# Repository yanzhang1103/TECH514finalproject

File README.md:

# TECH514finalproject
CatGuard
Proximity-Based Alert & Visualization System

A two-device proximity sensing system that detects how close an object or person is and provides intuitive physical feedback through a gauge needle and LED indicators. The system focuses on translating continuous proximity data into stable, non-screen-based feedback that can support spatial awareness and proximity alerts.

1. Sensor Device: Handheld Proximity Sensor

The sensor device is a compact, handheld proximity-sensing unit designed to detect nearby objects and transmit processed proximity data wirelessly to a separate display device. It emphasizes directional sensing and portable, USBC-powered operation.

Hardware Components

Microcontroller: ESP32-C3 

Distance Sensor: Sharp GP2Y0A21YK0F infrared distance sensor

Status Indicator: LED

Battery: 3.7V LiPo battery

How It Works

The infrared distance sensor continuously measures the distance between the device and nearby objects. The ESP32-C3 samples the analog sensor output and applies basic digital signal processing, including smoothing and thresholding, to reduce noise and generate a stable proximity level. This processed proximity data is transmitted to the display device using ESP-NOW.

2. Display Device: Proximity Gauge Display

The display device is a standalone physical interface that visualizes proximity information received from the sensor device. It provides continuous, intuitive feedback through a moving gauge needle and LED indicators and a buzzer.

Hardware Components

Microcontroller: ESP32-C3

Actuator: Stepper motor driving a gauge needle

Visual Indicator: LED

Sound Indicatior: Passive buzzer

User Input: Physical press button switch

Battery: 3.7V LiPo battery

Sketch

Safe range: >150 cm. Display sensor has no reaction within this range.
Warning range: 100-150 cm. The stepper motor needle rotates 90 degree to the middle/vertical position to indicate detection.
Alart range: <100 cm. The stepper motor needle rotates 180 degree all the way to the left to indicate detection, with LED light up and the buzzer buzzing.

How It Works

The display device receives proximity data from the sensor device via ESP-NOW. The ESP32-C3 maps the received proximity value to a corresponding needle angle and controls the stepper motor to move the gauge needle accordingly. LED and buzzer provide additional status feedback, such as indicating safe or alert proximity ranges.

User Interaction

A physical button allows basic user interaction, such as powering the device on or switching operating modes. The display continuously reflects proximity changes without requiring screen-based interaction.

3. System Architecture
3.1 Communication Diagram

The system consists of two independent, battery-powered devices connected via ESP-NOW. The sensor device acts as the server, while the display device functions as the client, receiving proximity updates in real time.

3.2 Workflow

diagram

The sensor device measures distance using the IR sensor.

Raw sensor data is filtered and processed on the ESP32-C3.

Processed proximity data is transmitted via ESP-NOW.

The display device receives the data and updates the gauge needle and LEDs accordingly.

Critical Components and PCB Design

Live Demo

https://github.com/user-attachments/assets/be7072d3-836d-4ff1-a74b-e89300e7f144

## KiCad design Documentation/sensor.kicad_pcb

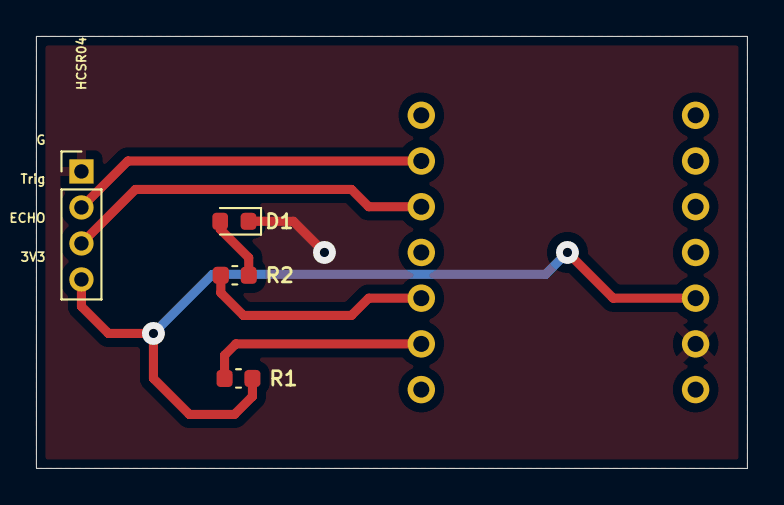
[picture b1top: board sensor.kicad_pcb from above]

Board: 2 copper layers, 39.5 x 24.0 mm, 5 parts (1 on the bottom side), 7 nets.

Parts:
D1: LED; LED_0603_1608Metric
J1: Conn_01x04; PinHeader_1x04_P2.00mm_Vertical
R1, R2: 10K; C_0603_1608Metric
U1: XIAO-ESP32-C3-DIP

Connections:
+3V3: J1.4, R1.2, U1.12 (3V3)
/Echo: J1.3, U1.5 (GPIO6_D4_SDA)
/Trig: J1.2, U1.6 (GPIO7_D5_SCL)
GND: D1.1 (K), J1.1, U1.13 (GND)
unnamed: D1.2 (A), R2.1
unnamed: R1.1, U1.2 (GPIO3_A1_D1)
unnamed: R2.2, U1.3 (GPIO4_A2_D2)

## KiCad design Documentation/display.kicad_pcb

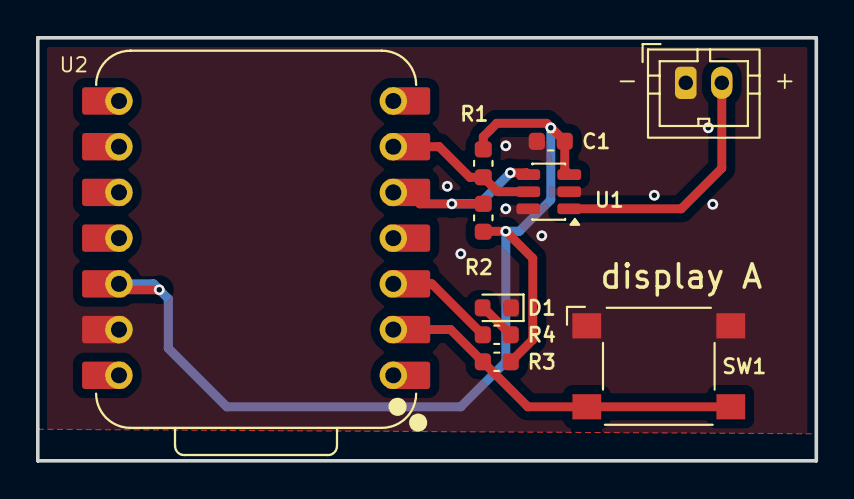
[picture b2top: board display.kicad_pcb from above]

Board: 2 copper layers, 43.2 x 23.5 mm, 10 parts (0 on the bottom side), 8 nets.

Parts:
C1: 100nf; C_0603_1608Metric
D1: LED; LED_0603_1608Metric
J1: Conn_01x02; TE_440054-2_1x02_P2.00mm_Vertical
R1, R2, R3, R4: 10K; C_0603_1608Metric
SW1: SW_Omron_B3FS; SW_SPST_Omron_B3FS-101xP
U1: MCP4725xxx-xCH; SOT-23-6
U2: XIAO-ESP32-C3-DIP

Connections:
+3V3: C1.2, R1.2, R2.2, R3.2, U1.3 (VDD), U2.12 (3V3)
GND: C1.1, D1.1 (K), J1.1, SW1.1, U1.2 (VSS), U1.6 (A0), U2.13 (GND)
unnamed: D1.2 (A), R4.1
unnamed: J1.2, U1.1 (VOUT)
unnamed: R1.1, U1.5 (SCL), U2.6 (GPIO7_D5_SCL)
unnamed: R2.1, U1.4 (SDA), U2.5 (GPIO6_D4_SDA)
unnamed: R3.1, SW1.2, U2.2 (GPIO3_A1_D1)
unnamed: R4.2, U2.3 (GPIO4_A2_D2)

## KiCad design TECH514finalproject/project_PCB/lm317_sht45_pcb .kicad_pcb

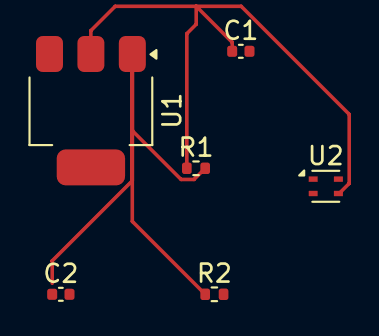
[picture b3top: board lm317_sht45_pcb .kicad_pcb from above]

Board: 2 copper layers, 6 parts (0 on the bottom side), 4 nets.

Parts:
C1: 0.1µF; C_0402_1005Metric
C2: 1µF; C_0402_1005Metric
R1: 240Ω; R_0402_1005Metric
R2: 390Ω; R_0402_1005Metric
U1: LM317_SOT-223; SOT-223-3_TabPin2
U2: SHT4x; Sensirion_DFN-4_1.5x1.5mm_P0.8mm_SHT4x_NoCentralPad

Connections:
GND: C1.2, C2.2, R2.2, U2.4 (VSS)
unnamed: R1.2, R2.1, U1.1 (ADJ)
unnamed: C1.1, R1.1, U1.2 (VO), U2.3 (VDD)
VCC: C2.1, U1.3 (VI)

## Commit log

2026-01-20 Create esp32-c3_datasheet
2026-01-27 schematic
2026-01-30 add kicad files
2026-01-30 Fix: add TECH514finalproject as normal folder
2026-01-30 organized folder
2026-02-05 Add power management lab code and measurements
2026-02-05 add sth
2026-03-18 Add project name 'CatGuard' to README
2026-03-18 Update README with images and sensor device info
    Added images and details about the sensor device and PCB design.
2026-03-18 Update README with project image and details
    Added an image and enhanced project description.
2026-03-18 Revise hardware details and communication method
    Updated communication method from BLE to ESP-NOW and removed motor driver mention.
2026-03-18 Revise README with updated device specifications
    Updated power source description for the sensor device and added details about the display device's buzzer and user input. Changed communication method from BLE to ESP-NOW for both devices.
2026-03-18 Add live demo link to README
    Added a link to the live demo of the project.
2026-03-18 Create display
